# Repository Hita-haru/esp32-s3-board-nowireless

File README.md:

# ESP32-S3-NoWireless-board
## Description
This is a devboard built using just the ESP32-S3 chip.
## Reason for Creation
Given the ESP32-S3’s AI capabilities and high performance, I wanted to create a program that connects a camera and analyzes its footage using  
AI. However, most inexpensive development boards lack technical compliance certification, and without it, powering them on in Japan would be illegal, forcing me to use a more expensive model.  
This makes it difficult to popularize affordable AI cameras, which is why I decided to build this.  

## How to assemble
1. Manufacture or order the components and circuit board.
2. Solder the components to the circuit board with all your might.
3. Connect it to a computer using a Type-C cable and flash the firmware.
4. After that, you’re free to use it however you like.

## How to Flash Firmware to Custom ESP32-S3 via Arduino IDE
1. Install Board Package
Open Arduino IDE and go to Preferences.

Add this URL to Additional Boards Manager URLs:

[https://raw.githubusercontent.com/espressif/arduino-esp32/gh-pages/package_esp32_index.json](https://raw.githubusercontent.com/espressif/arduino-esp32/gh-pages/package_esp32_index.json)

Open Tools > Board > Boards Manager, search for esp32, and install it.

2. Select Board Settings
Board: ESP32S3 Dev Module

USB CDC On Boot: Enabled (Crucial if using direct ESP32-S3 USB pins IO19/IO20 for Serial output)

Port: Select your board's COM port.

3. Enter Download (Bootloader) Mode
(If your custom board does not have an auto-reset circuit)

Press and HOLD the BOOT button (GPIO0).

Press and RELEASE the RESET (EN) button.

RELEASE the BOOT button.

4. Upload
Click the Upload button in Arduino IDE.

Once the upload is complete, press the RESET button once to run your code!

## Pictures
### Schematic

### PCB

### 3D

### Estimates
- JLCPCB  
  
**Shipping options**  
  
- LCSC  
  
**Shipping options**  

- Aliexpress  

## Cost details
### LCSC
- Subtotal for items  
*23.51* USD  
- Shipping fee (to Japan)  
*9.05* USD
- **Total**  
*32.50* USD (Including discount)  
### Aliexpress
- Subtotal for items  
*13.14* USD  
- Shipping fee (to Japan)  
*5.62* USD  
- **Total**  
*18.76* USD  
### JLCPCB
- Subtotal for items  
*4.00* USD  
- Shipping fee (to Japan)  
*1.00* USD (Including discount)  
- **Total**  
*5.00* USD (Including discount)  

## BOM
| No. | リファレンス (Designators) | 部品名 / 値 (Value) | フットプリント (Footprint) | 数量 | 単価 ($) | URL |
|:---|:---|:---|:---|:---|:---|:---|
| 1 | C13, C15, C12 | 4.7uF | C_0603_1608Metric_Pad1.08x0.95mm_HandSolder | 3 | 0.0675 | https://www.lcsc.com/product-detail/C90057.html?spm=wm.gwc.xh.0.cbm___wm.sy.ssl.gwc&lcsc_vid=QwBbVAVXQFcNVVcCQFkMUlFREQIMBFxQQ1YIUQIFR1MxVlNeR1JbUF1TQVhcVjtW |
| 2 | C16, C14, C19, C20, C24, C7, C22, C21, C23, C6, C3 | 0.1uF | C_0603_1608Metric_Pad1.08x0.95mm_HandSolder | 11 | 0.0161 | https://www.lcsc.com/product-detail/C85864.html?spm=wm.gwc.xh.1.cbm___wm.sy.ssl.gwc&lcsc_vid=QwBbVAVXQFcNVVcCQFkMUlFREQIMBFxQQ1YIUQIFR1MxVlNeR1JbUF1TQVhcVjtW |
| 3 | R7, R12, R11, R9, R1, R10, R8 | 10k | R_0603_1608Metric_Pad0.98x0.95mm_HandSolder | 7 | 0.0038 | https://www.lcsc.com/product-detail/C130232.html?spm=wm.gwc.xh.3.cbm___wm.sy.ssl.gwc&lcsc_vid=QwBbVAVXQFcNVVcCQFkMUlFREQIMBFxQQ1YIUQIFR1MxVlNeR1JbUF1TQVhcVjtW |
| 4 | C9, C8, C10, C17, C2, C18, C11, C1 | 10uF | C_0603_1608Metric_Pad1.08x0.95mm_HandSolder | 8 | 0.0230 | https://www.lcsc.com/product-detail/C7307463.html?spm=wm.gwc.dh.2.cbm___wm.sy.ssl.gwc&lcsc_vid=QwBbVAVXQFcNVVcCQFkMUlFREQIMBFxQQ1YIUQIFR1MxVlNeR1JbUF1TQVhcVjtW |
| 5 | U6 | NCP1117-1.5_SOT223 | SOT-223-3_TabPin2 | 1 | 0.0684 | https://www.lcsc.com/product-detail/C5380421.html?spm=wm.gwc.xh.4.cbm___wm.sy.ssl.gwc&lcsc_vid=QwBbVAVXQFcNVVcCQFkMUlFREQIMBFxQQ1YIUQIFR1MxVlNeR1JbUF1TQVhcVjtW |
| 6 | RST_SW | RST_SW | SW_Push_SPST_NO_Alps_SKRK | 1 | 0.1457 | https://www.lcsc.com/product-detail/C202388.html?spm=wm.gwc.xh.5.cbm___wm.sy.ssl.gwc&lcsc_vid=QwBbVAVXQFcNVVcCQFkMUlFREQIMBFxQQ1YIUQIFR1MxVlNeR1JbUF1TQVhcVjtW |
| 7 | U7 | MCP1700x-330xxTT | SOT-23 | 1 | 0.0886 | https://www.lcsc.com/product-detail/C7551026.html?spm=wm.gwc.xh.6.cbm___wm.sy.ssl.gwc&lcsc_vid=QwBbVAVXQFcNVVcCQFkMUlFREQIMBFxQQ1YIUQIFR1MxVlNeR1JbUF1TQVhcVjtW |
| 8 | Y1 | 40MHz | Crystal_SMD_3225-4Pin_3.2x2.5mm_HandSoldering | 1 | 0.2632 | https://www.lcsc.com/product-detail/C255943.html?spm=wm.gwc.xh.7.cbm___wm.sy.ssl.gwc&lcsc_vid=QwBbVAVXQFcNVVcCQFkMUlFREQIMBFxQQ1YIUQIFR1MxVlNeR1JbUF1TQVhcVjtW |
| 9 | R13 | 50 | R_0603_1608Metric_Pad0.98x0.95mm_HandSolder | 1 | 0.0312 | https://www.lcsc.com/product-detail/C849792.html?spm=wm.gwc.xh.8.cbm___wm.sy.ssl.gwc&lcsc_vid=QwBbVAVXQFcNVVcCQFkMUlFREQIMBFxQQ1YIUQIFR1MxVlNeR1JbUF1TQVhcVjtW |
| 10 | U1 | ESP32-S3 | QFN-56-1EP_7x7mm_P0.4mm_EP4x4mm | 1 | 1.64 | https://ja.aliexpress.com/item/1005012279323107.html?spm=a2g0o.cart.0.0.13f52e1aYLpvOE&mp=1&pdp_npi=6%40dis%21USD%21USD+10.40%21USD+8.22%21%21USD+7.81%21%21%21%40212e520f17803584957476551e54c5%2112000057974508459%21ct%21JP%216223408418%21%211%210%21&gatewayAdapt=glo2jpn |
| 11 | R6 | 1k | R_0603_1608Metric_Pad0.98x0.95mm_HandSolder | 1 | 0.0066 | https://www.lcsc.com/product-detail/C118155.html?spm=wm.gwc.xh.9.cbm___wm.sy.ssl.gwc&lcsc_vid=QwBbVAVXQFcNVVcCQFkMUlFREQIMBFxQQ1YIUQIFR1MxVlNeR1JbUF1TQVhcVjtW |
| 12 | C4, C5 | 15pF | C_0603_1608Metric_Pad1.08x0.95mm_HandSolder | 2 | 0.0066 | https://www.lcsc.com/product-detail/C71651.html?spm=wm.gwc.xh.10.cbm___wm.sy.ssl.gwc&lcsc_vid=QwBbVAVXQFcNVVcCQFkMUlFREQIMBFxQQ1YIUQIFR1MxVlNeR1JbUF1TQVhcVjtW |
| 13 | U2 | MCP1700x-280xxTT | SOT-23 | 1 | 0.0354 | https://www.lcsc.com/product-detail/C236702.html?spm=wm.gwc.xh.11.cbm___wm.sy.ssl.gwc&lcsc_vid=QwBbVAVXQFcNVVcCQFkMUlFREQIMBFxQQ1YIUQIFR1MxVlNeR1JbUF1TQVhcVjtW |
| 14 | BOOT_SW | BOOT_SW | SW_Push_SPST_NO_Alps_SKRK | 1 | 0.1457 | https://www.lcsc.com/product-detail/C202388.html?spm=wm.gwc.xh.5.cbm___wm.sy.ssl.gwc&lcsc_vid=QwBbVAVXQFcNVVcCQFkMUlFREQIMBFxQQ1YIUQIFR1MxVlNeR1JbUF1TQVhcVjtW |
| 15 | J1 | USB_C_Receptacle_USB2.0_14P | USB_C_Receptacle_HRO_TYPE-C-31-M-12 | 1 | 0.1870 | https://www.lcsc.com/product-detail/C165948.html?spm=wm.gwc.xh.12.cbm___wm.sy.ssl.gwc&lcsc_vid=QwBbVAVXQFcNVVcCQFkMUlFREQIMBFxQQ1YIUQIFR1MxVlNeR1JbUF1TQVhcVjtW |
| 16 | D7 | Green power light | LED_0805_2012Metric_Pad1.15x1.40mm_HandSolder | 1 | 0.0332 | https://www.lcsc.com/product-detail/C192319.html?spm=wm.gwc.xh.13.cbm___wm.sy.ssl.gwc&lcsc_vid=QwBbVAVXQFcNVVcCQFkMUlFREQIMBFxQQ1YIUQIFR1MxVlNeR1JbUF1TQVhcVjtW |
| 17 | R3, R2 | 5.1k | R_0603_1608Metric_Pad0.98x0.95mm_HandSolder | 2 | 0.0078 | https://www.lcsc.com/product-detail/C160048.html?spm=wm.gwc.xh.14.cbm___wm.sy.ssl.gwc&lcsc_vid=QwBbVAVXQFcNVVcCQFkMUlFREQIMBFxQQ1YIUQIFR1MxVlNeR1JbUF1TQVhcVjtW |
| 18 | U4 | ESP-PSRAM64H | SOIC-8_3.9x4.9mm_P1.27mm | 1 | 0.956 | https://ja.aliexpress.com/item/1005009178803030.html?spm=a2g0o.cart.0.0.13f52e1aYLpvOE&mp=1&pdp_npi=6%40dis%21USD%21USD+4.93%21USD+4.93%21%21USD+4.93%21%21%21%40212e520f17803584957476551e54c5%2112000048208912278%21ct%21JP%216223408418%21%211%210%21&gatewayAdapt=glo2jpn |
| 19 | D6, D2, D4, D5, D1 | ESD9B3.3ST5G | D_SOD-923 | 5 | 0.0154 | https://www.lcsc.com/product-detail/C51898359.html?spm=wm.gwc.xh.16.cbm___wm.sy.ssl.gwc&lcsc_vid=QwBbVAVXQFcNVVcCQFkMUlFREQIMBFxQQ1YIUQIFR1MxVlNeR1JbUF1TQVhcVjtW |
| 20 | J3 | Micro_SD_Card | microSD_HC_Molex_104031-0811 | 1 | 0.6804 | https://www.lcsc.com/product-detail/C585350.html?spm=wm.gwc.xh.18.cbm___wm.sy.ssl.gwc&lcsc_vid=QwBbVAVXQFcNVVcCQFkMUlFREQIMBFxQQ1YIUQIFR1MxVlNeR1JbUF1TQVhcVjtW |
| 21 | R5, R4 | 23 | R_0603_1608Metric_Pad0.98x0.95mm_HandSolder | 2 | 0.0020 | https://www.lcsc.com/product-detail/C2612468.html?spm=wm.gwc.xh.15.cbm___wm.sy.ssl.gwc&lcsc_vid=QwBbVAVXQFcNVVcCQFkMUlFREQIMBFxQQ1YIUQIFR1MxVlNeR1JbUF1TQVhcVjtW |
| 22 | U3 | W25Q128JVS | SOIC-8_5.3x5.3mm_P1.27mm | 1 | 2.6399 | https://www.lcsc.com/product-detail/C97521.html?spm=wm.gwc.xh.19.cbm___wm.sy.ssl.gwc&lcsc_vid=QwBbVAVXQFcNVVcCQFkMUlFREQIMBFxQQ1YIUQIFR1MxVlNeR1JbUF1TQVhcVjtW |
| 23 | J4 | Conn_01x08 | PinHeader_1x08_P2.54mm_Horizontal | 1 | 0.0734 | https://www.lcsc.com/product-detail/C7501270.html?spm=wm.gwc.xh.20.cbm___wm.sy.ssl.gwc&lcsc_vid=QwBbVAVXQFcNVVcCQFkMUlFREQIMBFxQQ1YIUQIFR1MxVlNeR1JbUF1TQVhcVjtW |
| 24 | J2 | OV2640 | Amphenol_F32Q-1A7x1-11024_1x24-1MP_P0.5mm_Horizontal | 1 | 2.1342 | https://www.lcsc.com/product-detail/C3168917.html?spm=wm.gwc.xh.21.cbm___wm.sy.ssl.gwc&lcsc_vid=QwBbVAVXQFcNVVcCQFkMUlFREQIMBFxQQ1YIUQIFR1MxVlNeR1JbUF1TQVhcVjtW |
| 25 | D3 | ESD9B5.0ST5G | D_SOD-923 | 1 | 0.0457 | https://www.lcsc.com/product-detail/C82326.html?spm=wm.gwc.xh.17.cbm___wm.sy.ssl.gwc&lcsc_vid=QwBbVAVXQFcNVVcCQFkMUlFREQIMBFxQQ1YIUQIFR1MxVlNeR1JbUF1TQVhcVjtW |
| 26 | - | PCB | - | 1 | 0.8 | https://cart.jlcpcb.com/jp/quote |

## Credits & Acknowledgements
This hardware design is based on / derived from the [ESP32-S3-EYE](https://github.com/espressif/esp-dev-kits) reference design created by **Espressif Systems**. Special thanks to Espressif for providing open-source hardware reference designs.

## Trademarks
- "ESP32", "ESP32-S3", and "Espressif" are registered trademarks or trademarks of **Espressif Systems (Shanghai) Co., Ltd.**
- All other trademarks and logos are the property of their respective owners.

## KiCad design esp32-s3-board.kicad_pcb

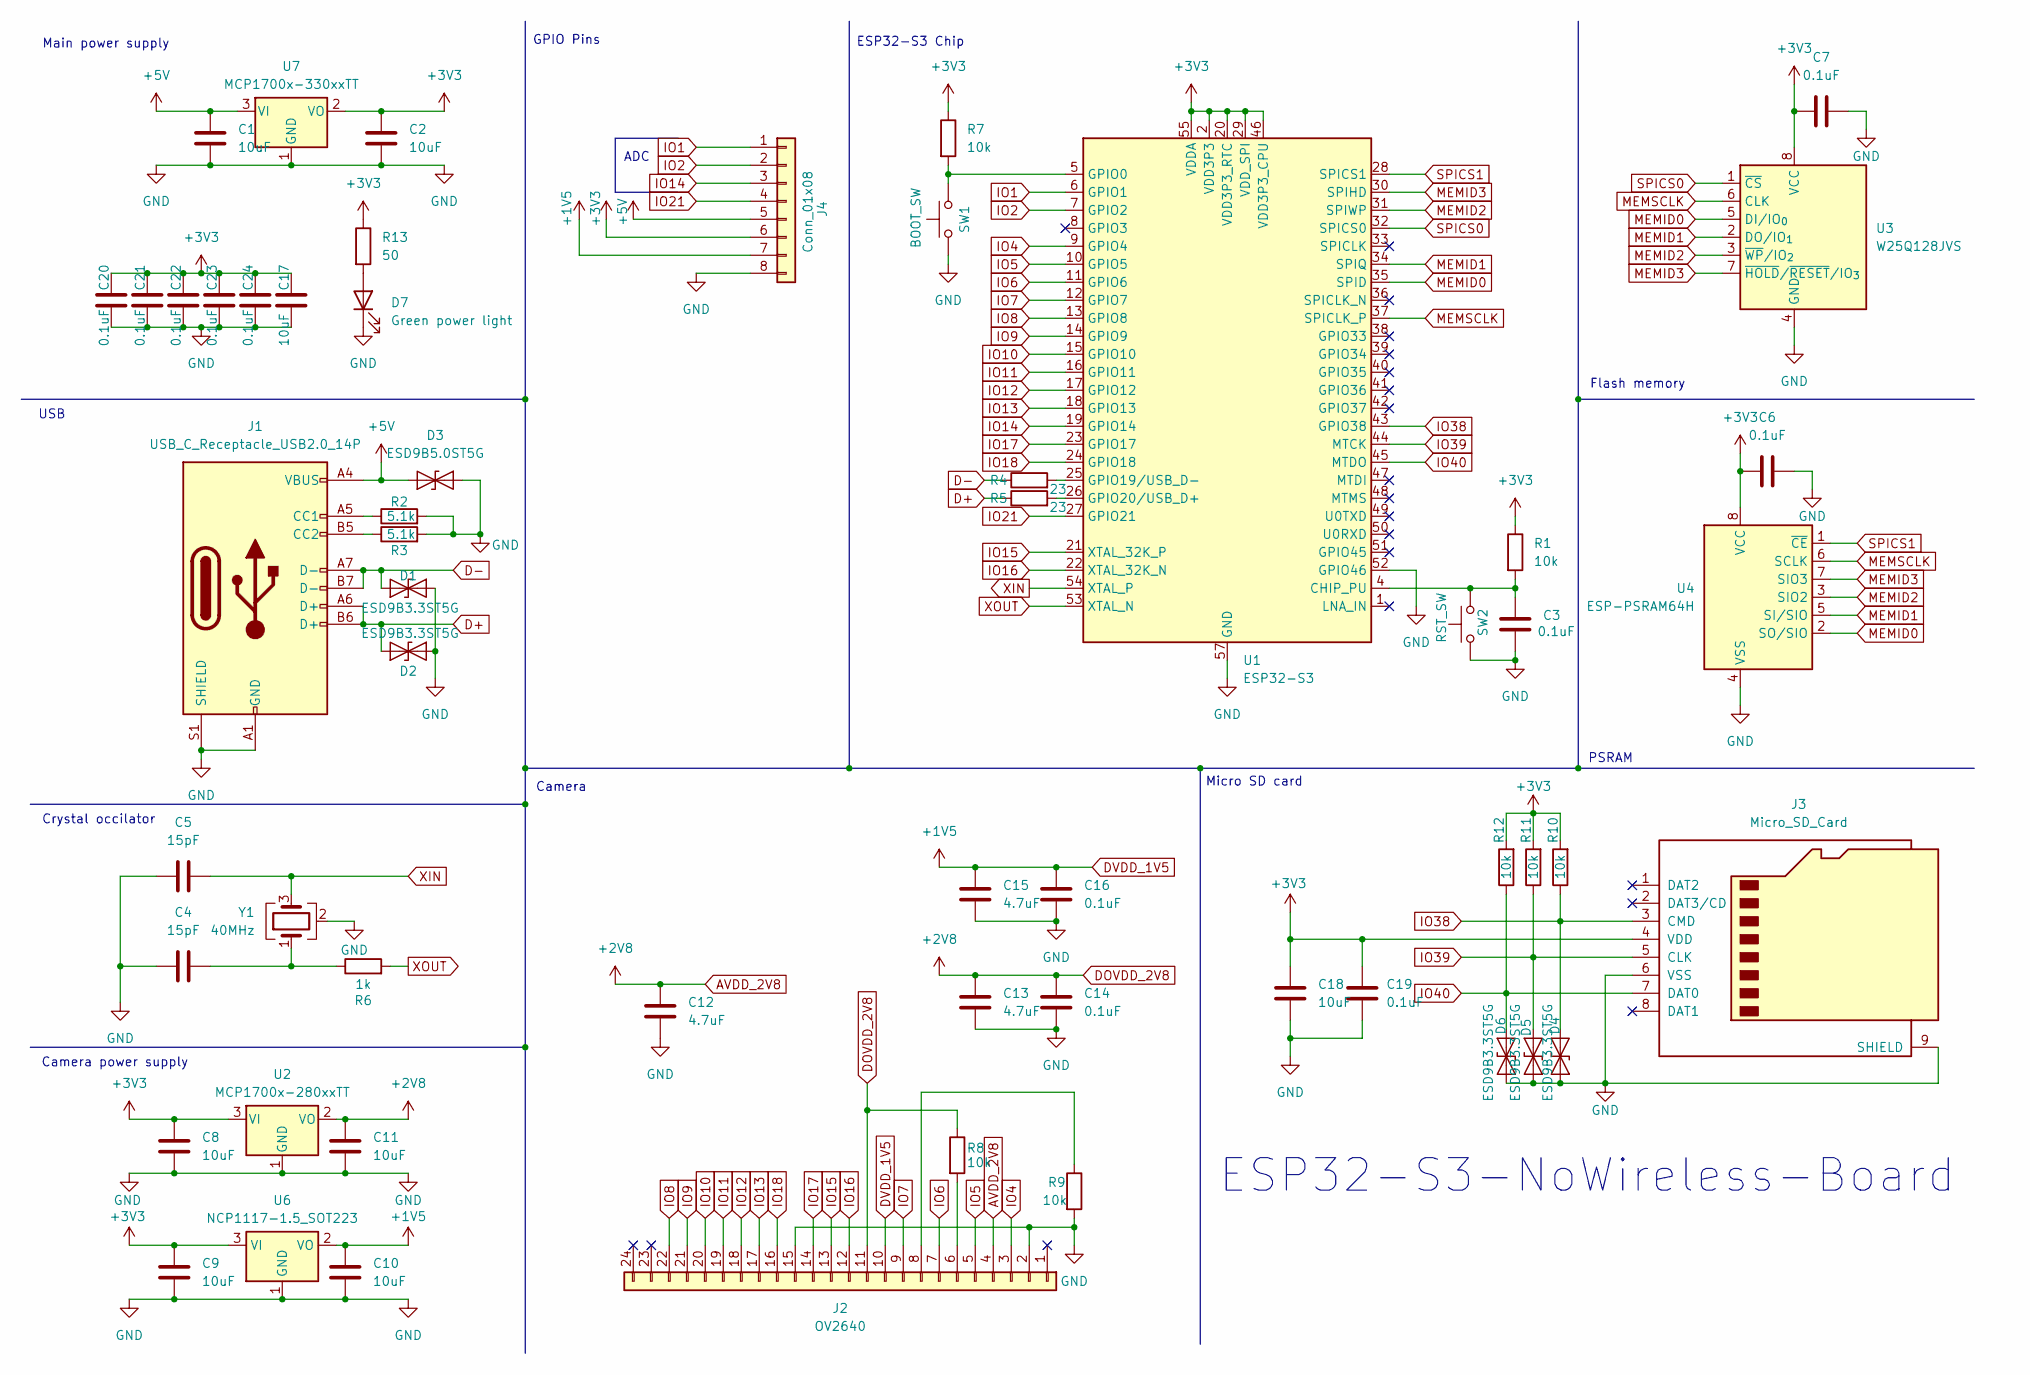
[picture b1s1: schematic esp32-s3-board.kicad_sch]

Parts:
C1, C2, C8, C9, C10, C11, C17, C18: 10uF; C_0603_1608Metric_Pad1.08x0.95mm_HandSolder
C3, C6, C7, C14, C16, C19, C20, C21, C22, C23, C24: 0.1uF; C_0603_1608Metric_Pad1.08x0.95mm_HandSolder
C4, C5: 15pF; C_0603_1608Metric_Pad1.08x0.95mm_HandSolder
C12, C13, C15: 4.7uF; C_0603_1608Metric_Pad1.08x0.95mm_HandSolder
D1, D2, D4, D5, D6: ESD9B3.3ST5G; D_SOD-923
D3: ESD9B5.0ST5G; D_SOD-923
D7: Green power light; LED_0805_2012Metric_Pad1.15x1.40mm_HandSolder
J1: USB_C_Receptacle_USB2.0_14P; USB_C_Receptacle_HRO_TYPE-C-31-M-12
J2: OV2640; Amphenol_F32Q-1A7x1-11024_1x24-1MP_P0.5mm_Horizontal
J3: Micro_SD_Card; microSD_HC_Molex_104031-0811
J4: Conn_01x08; PinHeader_1x08_P2.54mm_Horizontal
R1, R7, R8, R9, R10, R11, R12: 10k; R_0603_1608Metric_Pad0.98x0.95mm_HandSolder
R2, R3: 5.1k; R_0603_1608Metric_Pad0.98x0.95mm_HandSolder
R4, R5: 23; R_0603_1608Metric_Pad0.98x0.95mm_HandSolder
R6: 1k; R_0603_1608Metric_Pad0.98x0.95mm_HandSolder
R13: 50; R_0603_1608Metric_Pad0.98x0.95mm_HandSolder
SW1: BOOT_SW; SW_Push_SPST_NO_Alps_SKRK
SW2: RST_SW; SW_Push_SPST_NO_Alps_SKRK
U1: ESP32-S3; QFN-56-1EP_7x7mm_P0.4mm_EP4x4mm
U2: MCP1700x-280xxTT; SOT-23
U3: W25Q128JVS; SOIC-8_5.3x5.3mm_P1.27mm
U4: ESP-PSRAM64H; SOIC-8_3.9x4.9mm_P1.27mm
U6: NCP1117-1.5_SOT223; SOT-223-3_TabPin2
U7: MCP1700x-330xxTT; SOT-23
Y1: 40MHz; Crystal_SMD_3225-4Pin_3.2x2.5mm_HandSoldering

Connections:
+3V3: C2.1, C6.1, C7.1, C8.1, C9.1, C17.1, C18.1, C19.1, C20.1, C21.1, C22.1, C23.1, C24.1, J3.4 (VDD), J4.6, R1.1, R7.1, R10.2, R11.2, R12.2, R13.1, U1.2 (VDD3P3), U1.3 (VDD3P3), U1.20 (VDD3P3_RTC), U1.29 (VDD_SPI), U1.46 (VDD3P3_CPU), U1.55 (VDDA), U1.56 (VDDA), U2.3 (VI), U3.8 (VCC), U4.8 (VCC), U6.3 (VI), U7.2 (VO)
+5V: C1.1, D3.1 (A1), J1.A4 (VBUS), J1.A9 (VBUS), J1.B4 (VBUS), J1.B9 (VBUS), J4.5, U7.3 (VI)
AVDD_2V8: C11.1, C12.1, C13.1, C14.1, J2.4, J2.11, R8.1, U2.2 (VO)
D+: D2.1 (A1), J1.A6 (D+), J1.B6 (D+), R5.1
D-: D1.1 (A1), J1.A7 (D-), J1.B7 (D-), R4.1
DVDD_1V5: C10.1, C15.1, C16.1, J2.10, J4.7, U6.2 (VO)
GND: C1.2, C2.2, C3.2, C4.1, C5.1, C6.2, C7.2, C8.2, C9.2, C10.2, C11.2, C12.2, C13.2, C14.2, C15.2, C16.2, C17.2, C18.2, C19.2, C20.2, C21.2, C22.2, C23.2, C24.2, D1.2 (A2), D2.2 (A2), D3.2 (A2), D4.1 (A1), D5.1 (A1), D6.1 (A1), D7.1 (K), J1.A1 (GND), J1.A12 (GND), J1.B1 (GND), J1.B12 (GND), J1.S1 (SHIELD), J2.2, J2.15, J3.6 (VSS), J3.9 (SHIELD), J4.8, R2.2, R3.2, R9.2, SW1.1, SW2.1, U1.52 (GPIO46), U1.57 (GND), U2.1 (GND), U3.4 (GND), U4.4 (VSS), U6.1 (GND), U7.1 (GND), Y1.2 (G), Y1.4 (G); also elsewhere on the board
IO1: J4.1, U1.6 (GPIO1)
IO2: J4.2, U1.7 (GPIO2)
IO4: J2.3, U1.9 (GPIO4)
IO5: J2.5, U1.10 (GPIO5)
IO6: J2.7, U1.11 (GPIO6)
IO7: J2.9, U1.12 (GPIO7)
IO8: J2.22, U1.13 (GPIO8)
IO9: J2.21, U1.14 (GPIO9)
IO10: J2.20, U1.15 (GPIO10)
IO11: J2.19, U1.16 (GPIO11)
IO12: J2.18, U1.17 (GPIO12)
IO13: J2.17, U1.18 (GPIO13)
IO14: J4.3, U1.19 (GPIO14)
IO15: J2.13, U1.21 (XTAL_32K_P)
IO16: J2.12, U1.22 (XTAL_32K_N)
IO17: J2.14, U1.23 (GPIO17)
IO18: J2.16, U1.24 (GPIO18)
IO21: J4.4, U1.27 (GPIO21)
IO38: D4.2 (A2), J3.3 (CMD), R10.1, U1.43 (GPIO38)
IO39: D5.2 (A2), J3.5 (CLK), R11.1, U1.44 (MTCK)
IO40: D6.2 (A2), J3.7 (DAT0), R12.1, U1.45 (MTDO)
MEMID0: U1.35 (SPID), U3.5 (DI/IO_{0}), U4.2 (SO/SIO)
MEMID1: U1.34 (SPIQ), U3.2 (DO/IO_{1}), U4.5 (SI/SIO)
MEMID2: U1.31 (SPIWP), U3.3 (~WP/IO_{2}), U4.3 (SIO2)
MEMID3: U1.30 (SPIHD), U3.7 (~HOLD/~RESET/IO_{3}), U4.7 (SIO3)
MEMSCLK: U1.37 (SPICLK_P), U3.6 (CLK), U4.6 (SCLK)
unnamed: C4.2, R6.1, Y1.1
unnamed: D7.2 (A), R13.2
unnamed: J1.A5 (CC1), R2.1
unnamed: J1.B5 (CC2), R3.1
unnamed: J2.6, R8.2
unnamed: J2.8, R9.1
unnamed 39: C3.1, R1.2, SW2.2, U1.4 (CHIP_PU); also elsewhere on the board
unnamed 40: R7.2, SW1.2, U1.5 (GPIO0); also elsewhere on the board
unnamed: R4.2, U1.25 (GPIO19/USB_D-)
unnamed: R5.2, U1.26 (GPIO20/USB_D+)
SPICS0: U1.32 (SPICS0), U3.1 (~CS)
SPICS1: U1.28 (SPICS1), U4.1 (~CE)
XIN: C5.2, U1.54 (XTAL_P), Y1.3
XOUT: R6.2, U1.53 (XTAL_N)

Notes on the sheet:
Crystal occilator
Camera power supply
Main power supply
ESP32-S3 Chip
Camera
ESP32-S3-NoWireless-Board
USB
Flash memory
ADC
GPIO Pins
Micro SD card
PSRAM

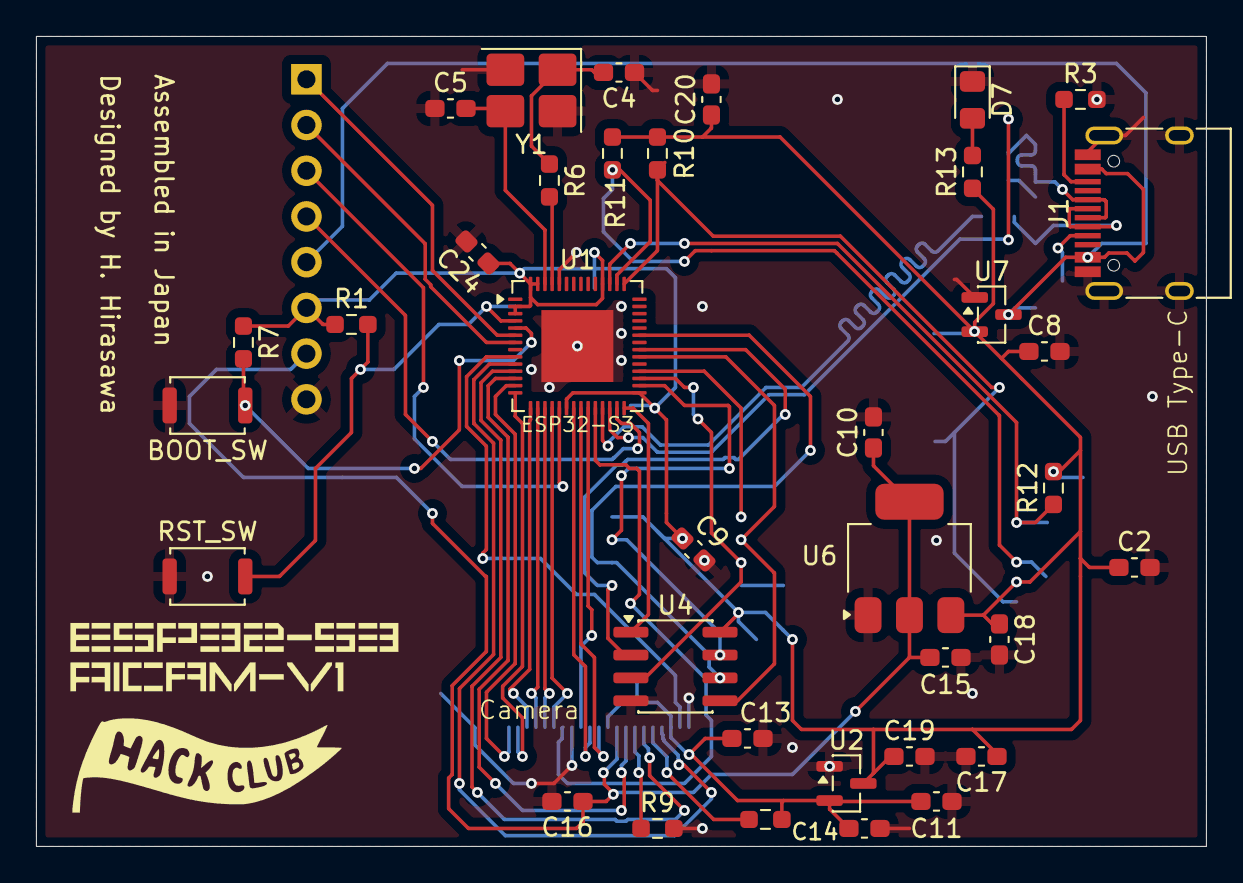
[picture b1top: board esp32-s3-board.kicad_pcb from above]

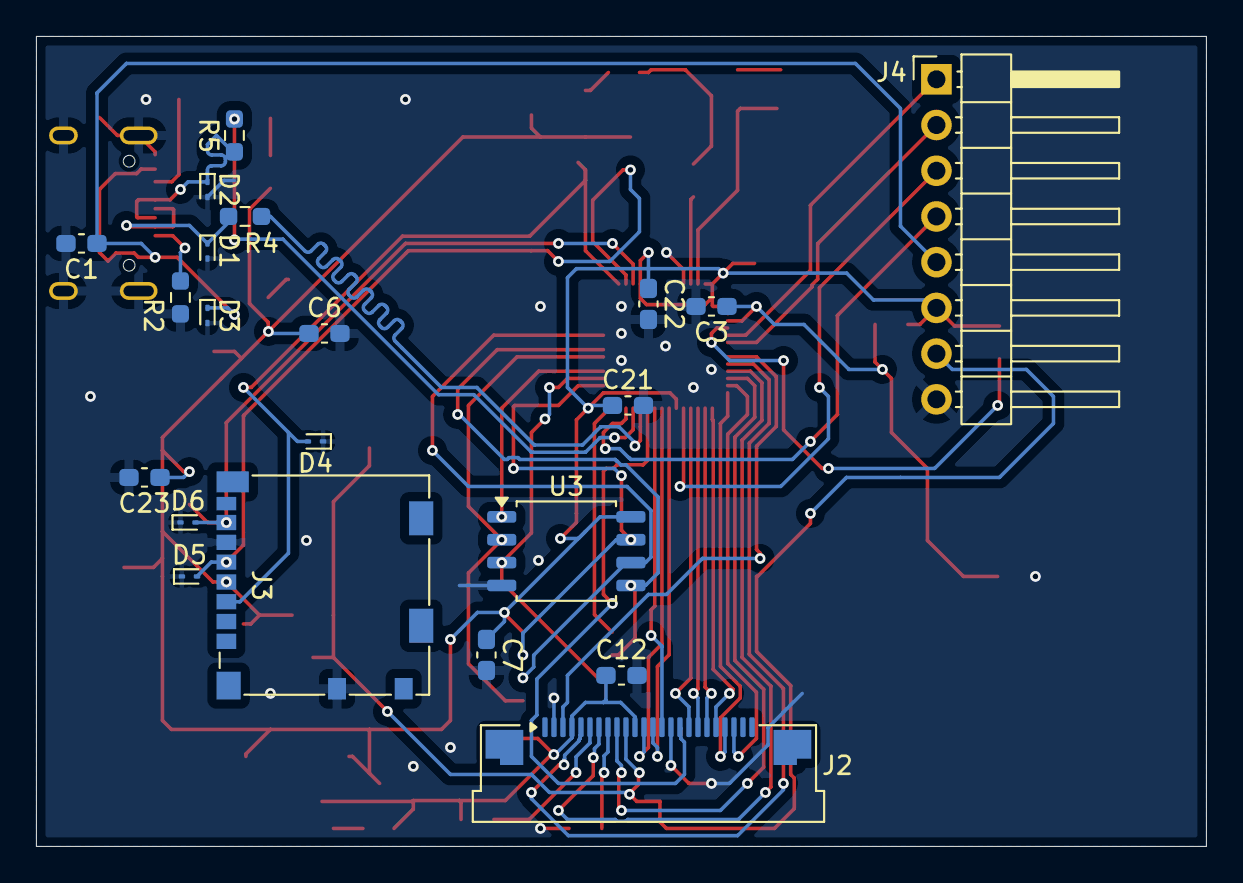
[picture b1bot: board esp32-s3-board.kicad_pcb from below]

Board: 2 copper layers, 65.0 x 45.0 mm, 57 parts (21 on the bottom side), 47 nets.

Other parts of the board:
BOOT_SW: BOOT_SW; SW_Push_SPST_NO_Alps_SKRK
RST_SW: RST_SW; SW_Push_SPST_NO_Alps_SKRK

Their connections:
GND: BOOT_SW.1, RST_SW.1; also elsewhere on the board
unnamed 39: RST_SW.2; also elsewhere on the board
unnamed 40: BOOT_SW.2; also elsewhere on the board

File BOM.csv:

1,"C13,C15,C12","C_0603_1608Metric_Pad1.08x0.95mm_HandSolder",3,"4.7uF",,,
2,"C16,C14,C19,C20,C24,C7,C22,C21,C23,C6,C3","C_0603_1608Metric_Pad1.08x0.95mm_HandSolder",11,"0.1uF",,,
3,"R7,R12,R11,R9,R1,R10,R8","R_0603_1608Metric_Pad0.98x0.95mm_HandSolder",7,"10k",,,
4,"C9,C8,C10,C17,C2,C18,C11,C1","C_0603_1608Metric_Pad1.08x0.95mm_HandSolder",8,"10uF",,,
5,"U6","SOT-223-3_TabPin2",1,"NCP1117-1.5_SOT223",,,
6,"RST_SW","SW_Push_SPST_NO_Alps_SKRK",1,"RST_SW",,,
7,"U7","SOT-23",1,"MCP1700x-330xxTT",,,
8,"Y1","Crystal_SMD_3225-4Pin_3.2x2.5mm_HandSoldering",1,"40MHz",,,
9,"R13","R_0603_1608Metric_Pad0.98x0.95mm_HandSolder",1,"50",,,
10,"U1","QFN-56-1EP_7x7mm_P0.4mm_EP4x4mm",1,"ESP32-S3",,,
11,"R6","R_0603_1608Metric_Pad0.98x0.95mm_HandSolder",1,"1k",,,
12,"C4,C5","C_0603_1608Metric_Pad1.08x0.95mm_HandSolder",2,"15pF",,,
13,"U2","SOT-23",1,"MCP1700x-280xxTT",,,
14,"BOOT_SW","SW_Push_SPST_NO_Alps_SKRK",1,"BOOT_SW",,,
15,"J1","USB_C_Receptacle_HRO_TYPE-C-31-M-12",1,"USB_C_Receptacle_USB2.0_14P",,,
16,"D7","LED_0805_2012Metric_Pad1.15x1.40mm_HandSolder",1,"Green power light",,,
17,"R3,R2","R_0603_1608Metric_Pad0.98x0.95mm_HandSolder",2,"5.1k",,,
21,"R5,R4","R_0603_1608Metric_Pad0.98x0.95mm_HandSolder",2,"23",,,
18,"U4","SOIC-8_3.9x4.9mm_P1.27mm",1,"ESP-PSRAM64H",,,
19,"D6,D2,D4,D5,D1","D_SOD-923",5,"ESD9B3.3ST5G",,,
25,"D3","D_SOD-923",1,"ESD9B5.0ST5G",,,
20,"J3","microSD_HC_Molex_104031-0811",1,"Micro_SD_Card",,,
22,"U3","SOIC-8_5.3x5.3mm_P1.27mm",1,"W25Q128JVS",,,
23,"J4","PinHeader_1x08_P2.54mm_Horizontal",1,"Conn_01x08",,,
24,"J2","Amphenol_F32Q-1A7x1-11024_1x24-1MP_P0.5mm_Horizontal",1,"OV2640",,,

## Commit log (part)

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2026-05-21 Add JOURNAL.md
2026-05-21 Add journal
2026-05-21 Add time to journal
2026-05-22 Added journal
2026-05-23 Editted journal
2026-05-27 Finished writing schematic
2026-05-28 Assigned footprint
2026-05-29 Routed PCB for the first time
2026-05-30 Finished routing pcb
2026-05-31 Created JLCPCB estimate
2026-06-01 Created LCSC and Aliexpress estimates
2026-06-01 Added readme
2026-06-01 Fixed journal
2026-06-01 Added 3D preview
2026-06-02 Fixed README.md and fabrication files
2026-06-06 Updated JOURNAL.md
